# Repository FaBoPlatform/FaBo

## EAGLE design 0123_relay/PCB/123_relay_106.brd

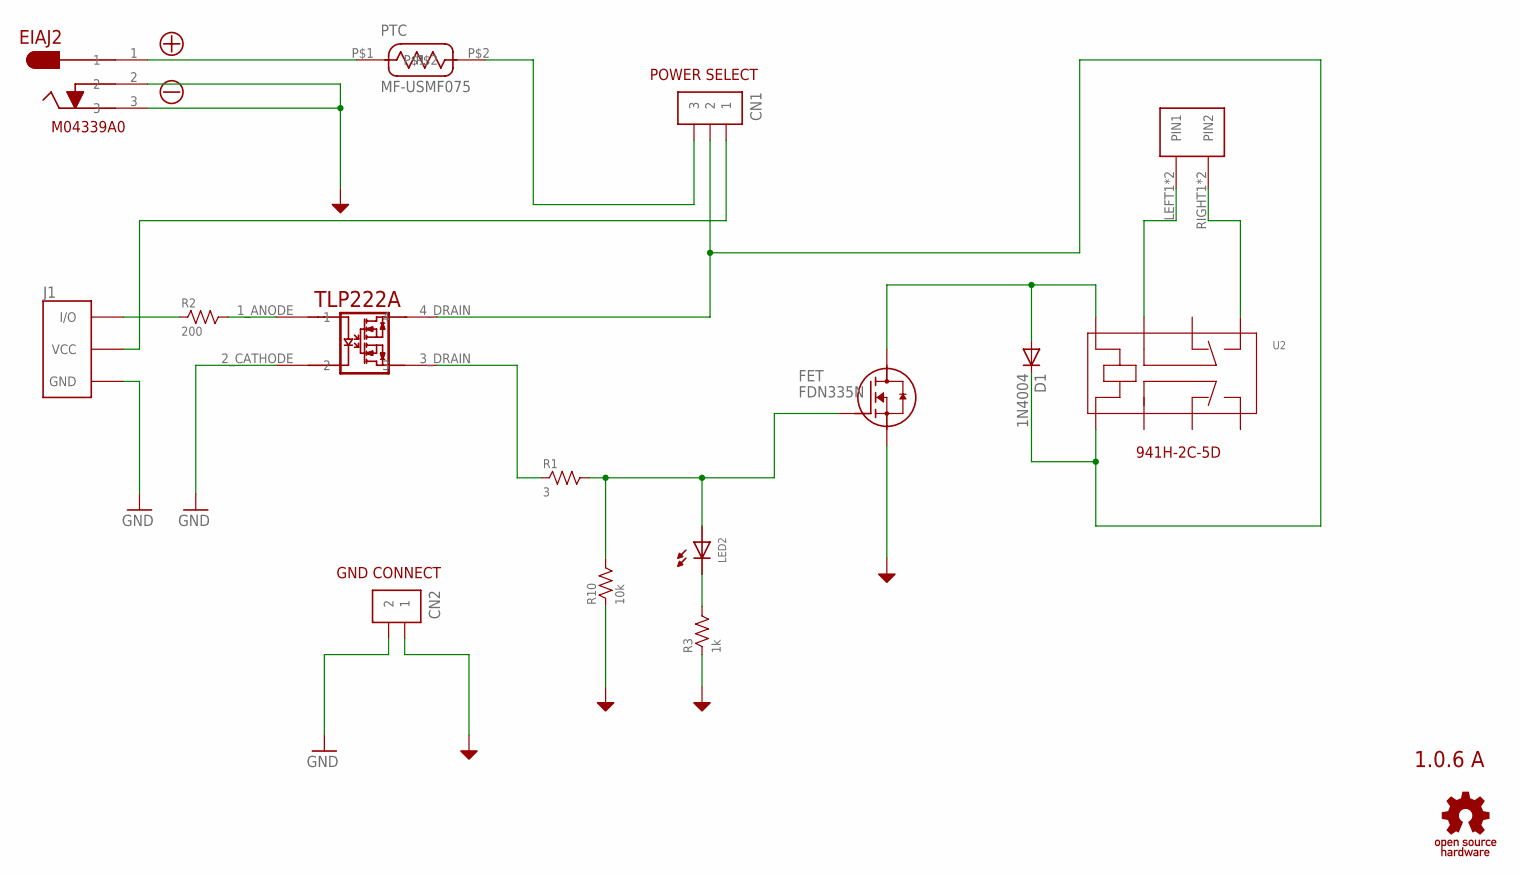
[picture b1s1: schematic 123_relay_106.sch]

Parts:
CN1: PIN_HEADER_1X3; PIN_1X3
CN2: PIN_HEADER_1X2; PIN_1X2
D1: 1N4004; DO41-10
FET: FDN335N; FDN335
J1: FABO_BRICK_3PIN-LONG; FABO_BRICK_3PIN_LONG
LED2: LED-0603; 0603
PTC: MF-USMF075
R1: 3; 0603-NARROW
R2: 200; 0603-NARROW
R3: 1k; 0603-NARROW
R10: 10k; 0603-NARROW
RELAY2: ML-1400-S1
U2: 941-RELAY; 941_RELAY
U$2: LOGO_OSHW-M_BOTTOM; LOGO_OSHW_M_BOTTOM
U$7: M04339A0
U$9: TLP222A

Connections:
GND: CN2.2, J1.GND, U$9.2_CATHODE (2)
GND_SECONDARY: CN2.1, FET.2:S (S), R3.1, R10.1, U$7.2, U$7.3
unnamed: J1.I/O, R2.1
unnamed: RELAY2.LEFT1 (PIN1), RELAY2.LEFT2 (PIN1), U2.13
unnamed: RELAY2.RIGHT1 (PIN2), RELAY2.RIGHT2 (PIN2), U2.9
unnamed: R2.2, U$9.1_ANODE (1)
unnamed: CN1.1, J1.VCC
unnamed: LED2.CATHODE, R3.2
unnamed: CN1.3, PTC.P$2
unnamed: CN1.2, D1.C, U2.1, U$9.4_DRAIN (4)
unnamed: PTC.P$1, U$7.1
unnamed: D1.A, FET.3:D (D), U2.16
unnamed: R1.1, U$9.3_DRAIN (3)
RELAY02: FET.1:G (G), LED2.ANODE, R1.2, R10.2

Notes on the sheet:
1.0.6 A
POWER SELECT
GND CONNECT
941H-2C-5D

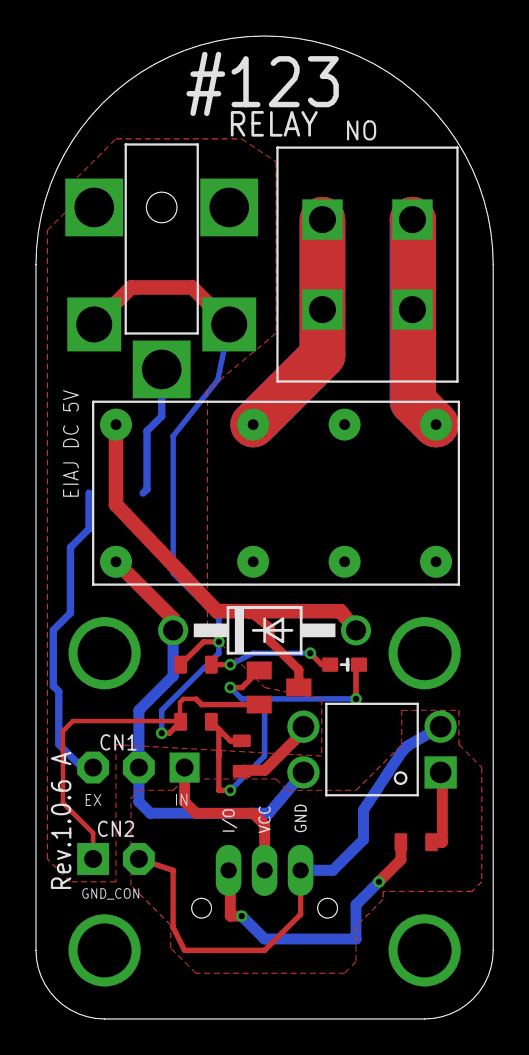
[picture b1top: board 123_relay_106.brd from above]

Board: 2 copper layers, 25.4 x 54.6 mm, 16 parts (1 on the bottom side), 14 nets.

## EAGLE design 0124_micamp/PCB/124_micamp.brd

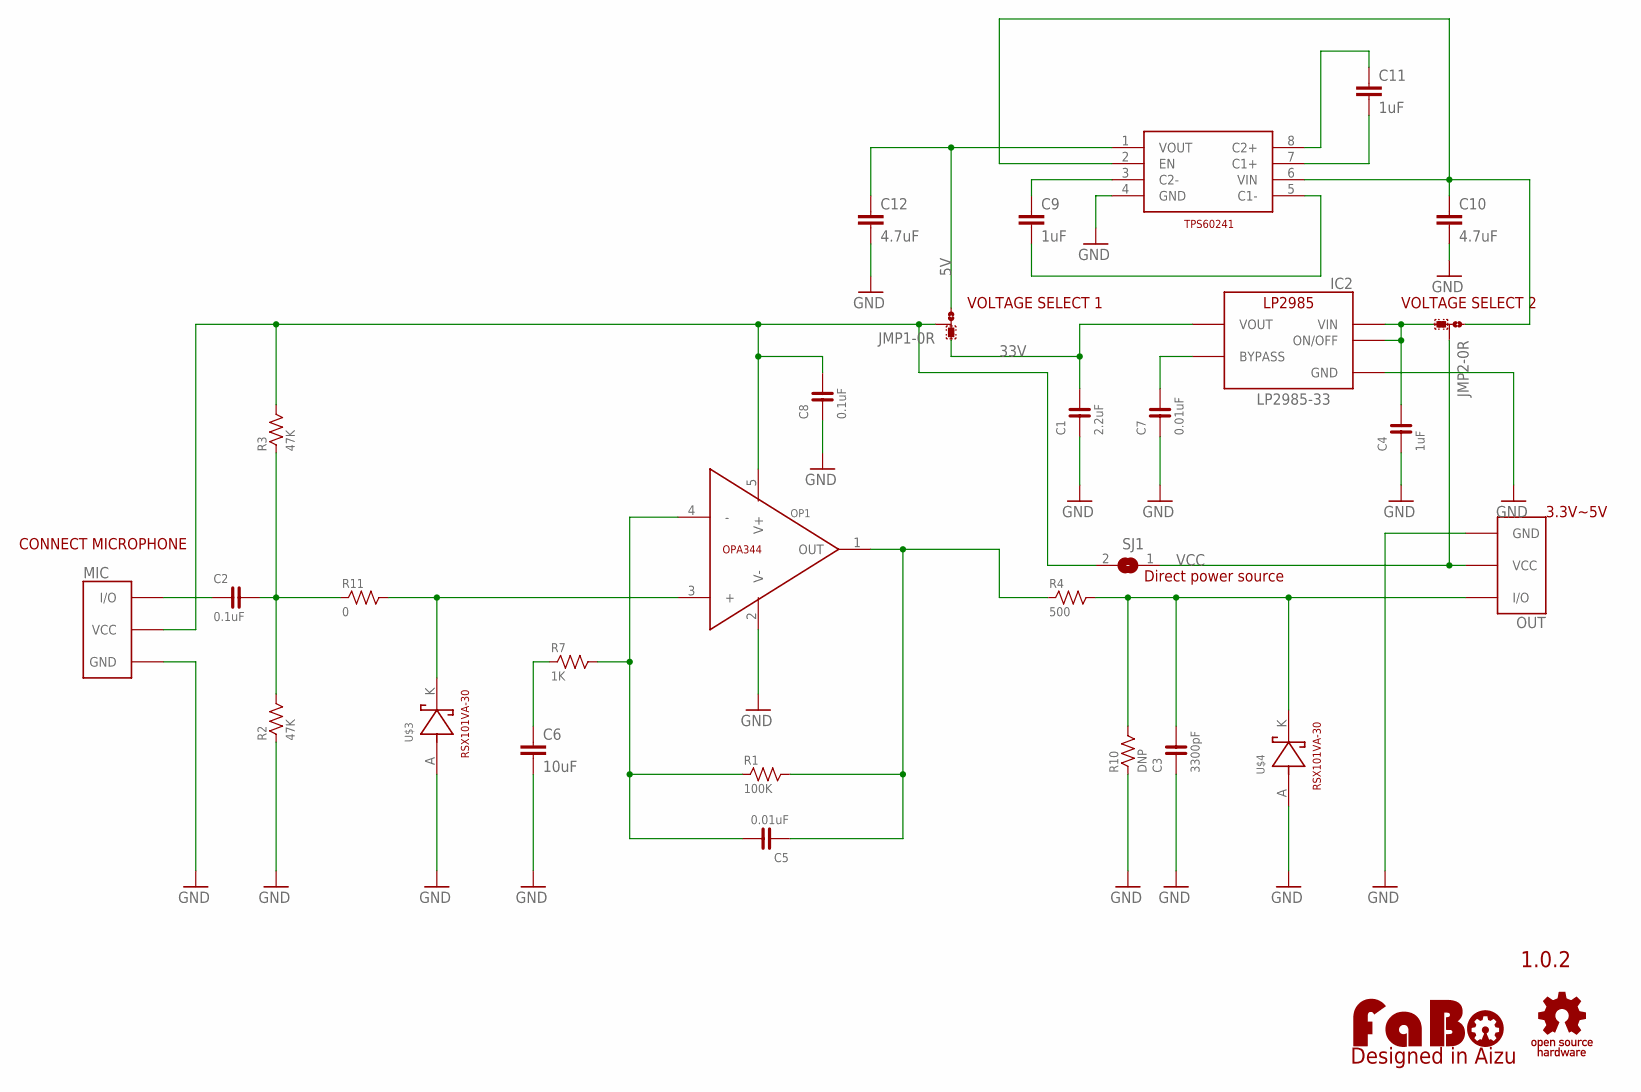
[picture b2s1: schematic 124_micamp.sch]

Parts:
C1: 2.2uF; 0603
C2, C8: 0.1uF; 0603
C3: 3300pF; 0603
C4: 1uF; 0603
C5, C7: 0.01uF; 0603
C6: 10uF; C1206K
C9, C11: 1uF; C2012
C10, C12: 4.7uF; C2012
IC2: LP2985-33; SOT-23-5
JMP1, JMP2: 0R-JUMPA; A0R-JMP
LOGO1: LOGO_FABO-S; LOGO_FABO_S
MIC: FABO_BRICK_3PIN-S03B-PASK-2; FABO_BRICK_3PIN_S03B-PASK-2
OP1: OPA344; SOT23-5
OUT: FABO_BRICK_3PIN-S03B-PASK-2; FABO_BRICK_3PIN_S03B-PASK-2
R1: 100K; 0603
R2, R3: 47K; 0603
R4: 500; 0603
R7: 1K; 0603
R10: DNP; 0603
R11: 0; 0603
SJ1: SJ
U$2: LOGO_OSHW-S_BOTTOM; LOGO_OSHW_S_BOTTOM
U$3, U$4: RSX101VA-30
U$5: TPS60241(VSSOP8); VSSOP8

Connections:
5V: C12.1, JMP1.3, U$5.1 (VOUT)
33V: C1.2, IC2.5 (VOUT), JMP1.1
GND: C1.1, C3.1, C4.1, C6.2, C7.1, C8.1, C10.2, C12.2, IC2.2 (GND), MIC.GND, OP1.2 (V-), OUT.GND, R2.1, R10.1, U$3.A (ANODE), U$4.A (ANODE), U$5.4 (GND)
unnamed: OP1.3 (+), R11.2, U$3.K (CATHODE)
unnamed: C2.1, MIC.I/O
unnamed: C5.2, OP1.4 (-), R1.1, R7.2
unnamed: C6.1, R7.1
unnamed: C5.1, OP1.1 (OUT), R1.2, R4.1
unnamed: C7.2, IC2.4 (BYPASS)
unnamed: C2.2, R2.2, R3.1, R11.1
unnamed: C3.2, OUT.I/O, R4.2, R10.2, U$4.K (CATHODE)
unnamed: C9.1, U$5.3 (C2-)
unnamed: C9.2, U$5.5 (C1-)
unnamed: C11.1, U$5.8 (C2+)
unnamed: C11.2, U$5.7 (C1+)
unnamed: C10.1, JMP2.1, U$5.2 (EN), U$5.6 (VIN)
unnamed: C4.2, IC2.1 (VIN), IC2.3 (ON/OFF), JMP2.3
VCC: JMP2.2, OUT.VCC, SJ1.1
VCC_ON: C8.2, JMP1.2, MIC.VCC, OP1.5 (V+), R3.2, SJ1.2

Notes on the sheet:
LP2985-33
Direct power source
VOLTAGE SELECT 1
VOLTAGE SELECT 2
3.3V~5V
1.0.2
CONNECT MICROPHONE

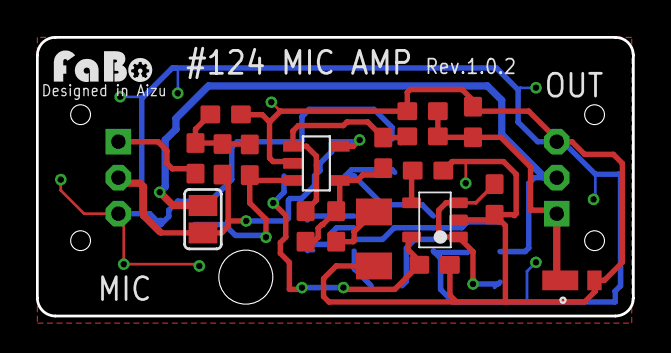
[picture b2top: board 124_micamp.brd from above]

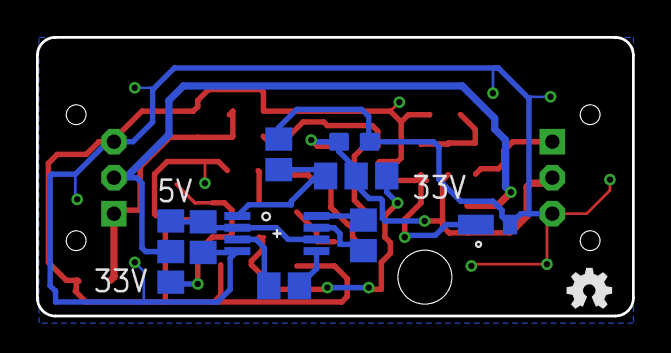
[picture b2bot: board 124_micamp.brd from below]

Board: 2 copper layers, 33.1 x 15.5 mm, 31 parts (9 on the bottom side), 19 nets.

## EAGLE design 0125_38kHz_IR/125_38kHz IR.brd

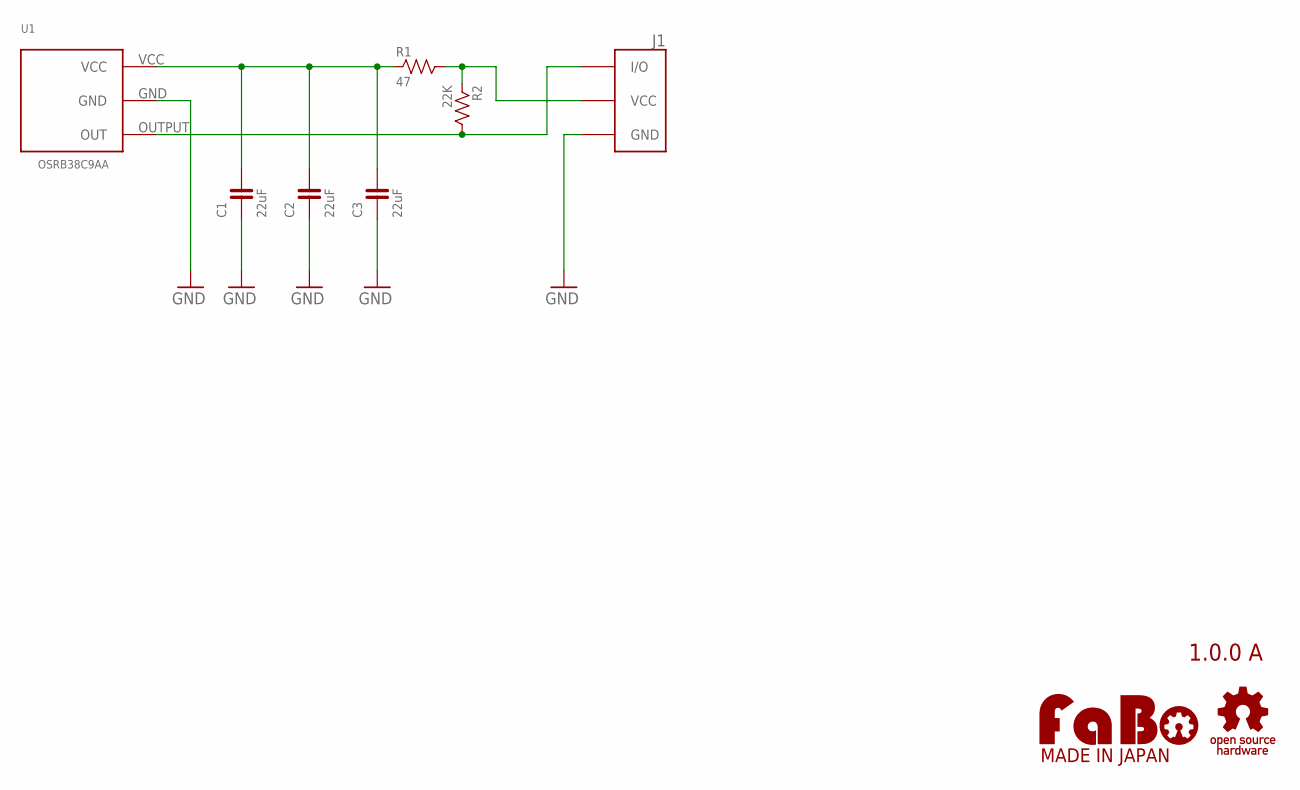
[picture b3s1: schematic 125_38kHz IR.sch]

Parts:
C1, C2, C3: 22uF; 0805
J1: FABO_BRICK_3PIN
R1: 47; 0603
R2: 22K; 0603
U1: OSRB38C9AA
U$2: LOGO_OSHW-M; LOGO_OSHW_M
U$3: LOGO_FABO-M_BOTTOM; LOGO_FABO_MS_BOTTOM

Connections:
GND: C1.1, C2.1, C3.1, J1.GND, U1.GND
unnamed: C1.2, C2.2, C3.2, R1.1, U1.VCC
unnamed: J1.VCC, R1.2, R2.1
unnamed: J1.I/O, R2.2, U1.OUTPUT (OUT)

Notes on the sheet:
1.0.0 A

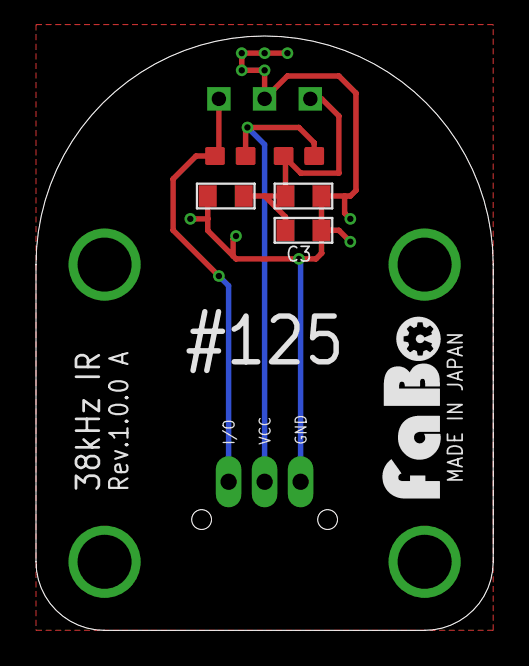
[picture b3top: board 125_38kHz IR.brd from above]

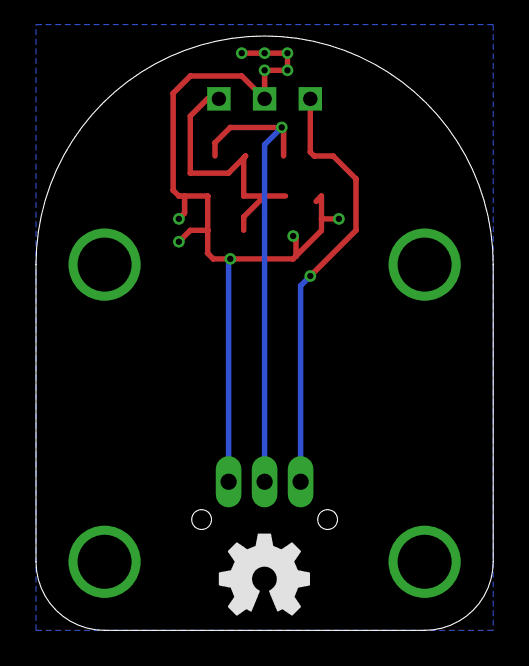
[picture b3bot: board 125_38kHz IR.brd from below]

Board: 2 copper layers, 25.4 x 33.0 mm, 9 parts (2 on the bottom side), 4 nets.

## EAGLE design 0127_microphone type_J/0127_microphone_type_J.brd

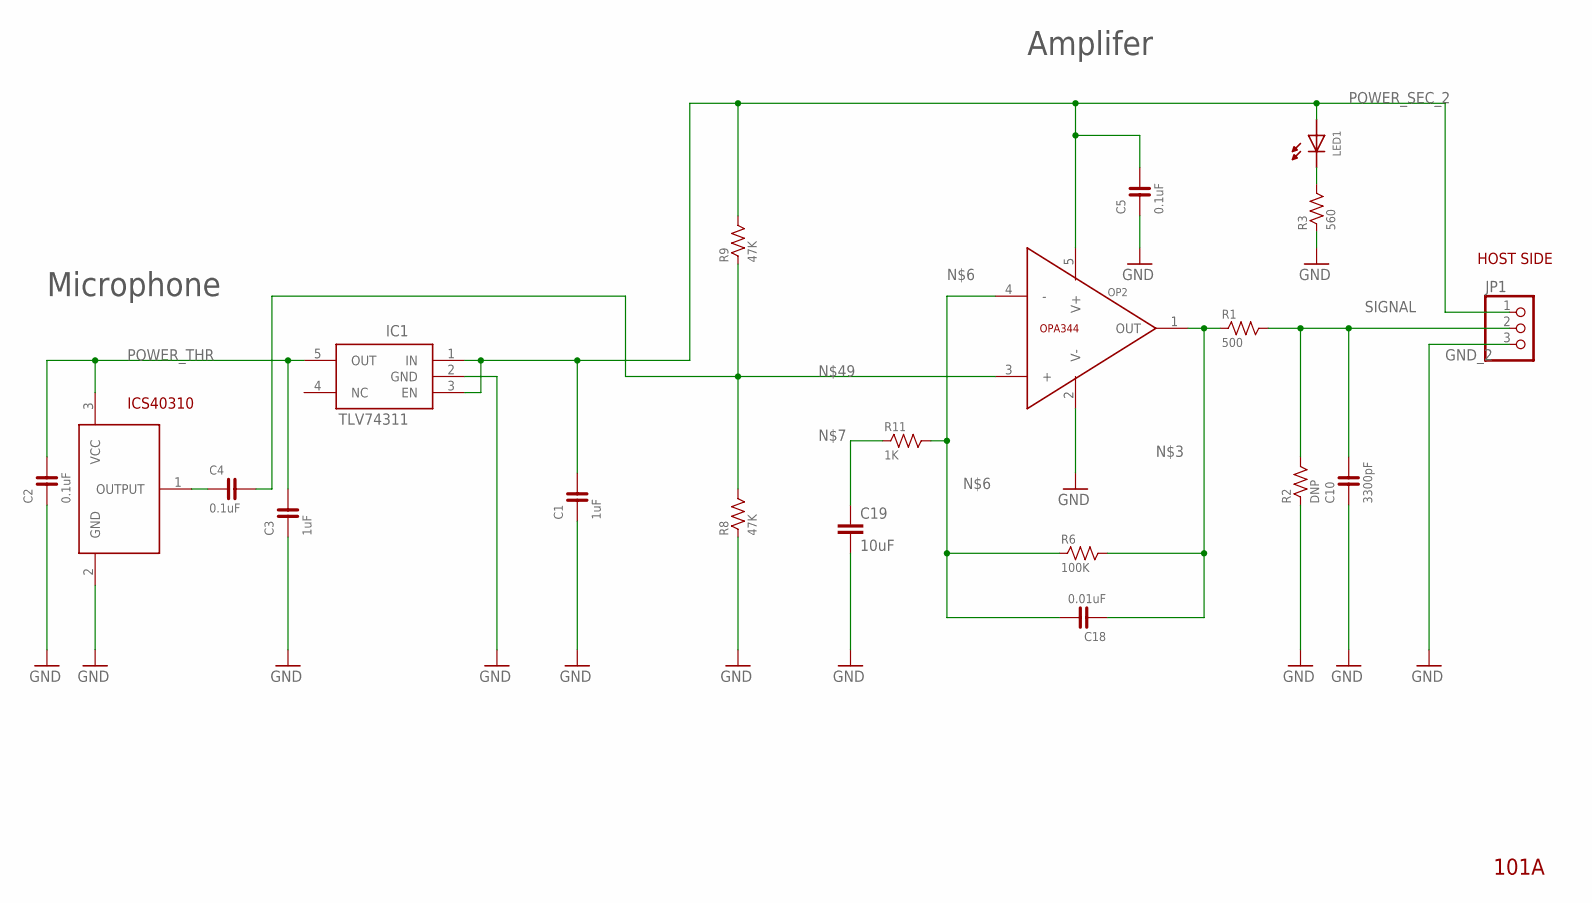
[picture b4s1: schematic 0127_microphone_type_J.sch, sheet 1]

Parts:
C1, C3: 1uF; 0603
C2, C4, C5: 0.1uF; 0603
C10: 3300pF; 0603
C18: 0.01uF; 0603
C19: 10uF; C1206K
IC1: TLV74311; SOT-23-5
ICS40310: ANALOG-MICICS40310; ICS40310
JP1: PINHD-1X3; 1X03
LED1: LED-0603-NARROW; 0603-NARROW
OP2: OPA344; SOT23-5
R1: 500; 0603
R2: DNP; 0603
R3: 560; 0603
R6: 100K; 0603
R8, R9: 47K; 0603
R11: 1K; 0603

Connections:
GND_2: C1.1, C2.1, C3.1, C5.1, C10.1, C19.2, IC1.2 (GND), ICS40310.2 (GND), JP1.3, OP2.2 (V-), R2.1, R3.1, R8.1
unnamed: C18.1, OP2.1 (OUT), R1.1, R6.2
unnamed: C4.1, ICS40310.1 (OUTPUT)
unnamed: LED1.CATHODE, R3.2
unnamed: C18.2, OP2.4 (-), R6.1, R11.2
unnamed: C19.1, R11.1
unnamed: C4.2, OP2.3 (+), R8.2, R9.1
POWER_SEC_2: C1.2, C5.2, IC1.1 (IN), IC1.3 (EN), JP1.1, LED1.ANODE, OP2.5 (V+), R9.2
POWER_THR: C2.2, C3.2, IC1.5 (OUT), ICS40310.3 (VCC)
SIGNAL: C10.2, JP1.2, R1.2, R2.2

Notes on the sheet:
Microphone
ICS40310
101A
Amplifer
HOST SIDE

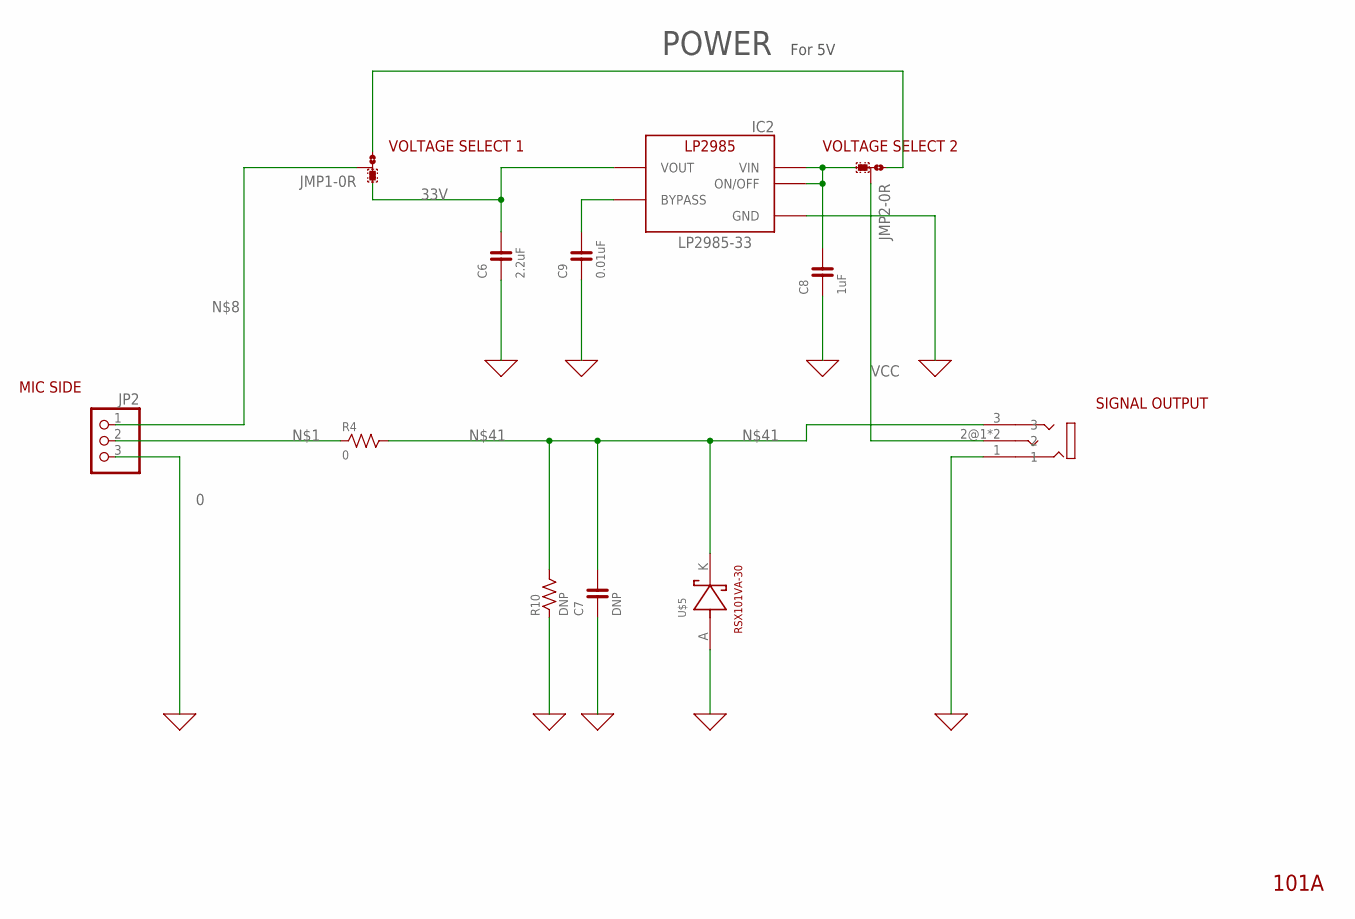
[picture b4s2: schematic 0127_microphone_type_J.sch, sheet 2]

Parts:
C6: 2.2uF; 0603
C7: DNP; 0603
C8: 1uF; 0603
C9: 0.01uF; 0603
IC2: LP2985-33; SOT-23-5
JMP1, JMP2: 0R-JUMPA; A0R-JMP
JP2: PINHD-1X3; 1X03
R4: 0; 0603
R10: DNP; 0603
U$4: MJ8435
U$5: RSX101VA-30

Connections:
0: C6.1, C7.1, C8.1, C9.1, IC2.2 (GND), JP2.3, R10.1, U$4.1, U$5.A (ANODE)
33V: C6.2, IC2.5 (VOUT), JMP1.1
unnamed: JP2.2, R4.1
unnamed: JMP1.3, JMP2.1
unnamed: JMP1.2, JP2.1
unnamed: C7.2, R4.2, R10.2, U$4.3, U$5.K (CATHODE)
unnamed: C9.2, IC2.4 (BYPASS)
unnamed: C8.2, IC2.1 (VIN), IC2.3 (ON/OFF), JMP2.3
VCC: JMP2.2, U$4.2@1 (2), U$4.2@2 (2)

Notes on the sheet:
LP2985-33
VOLTAGE SELECT 1
VOLTAGE SELECT 2
101A
SIGNAL OUTPUT
MIC SIDE
POWER
For 5V

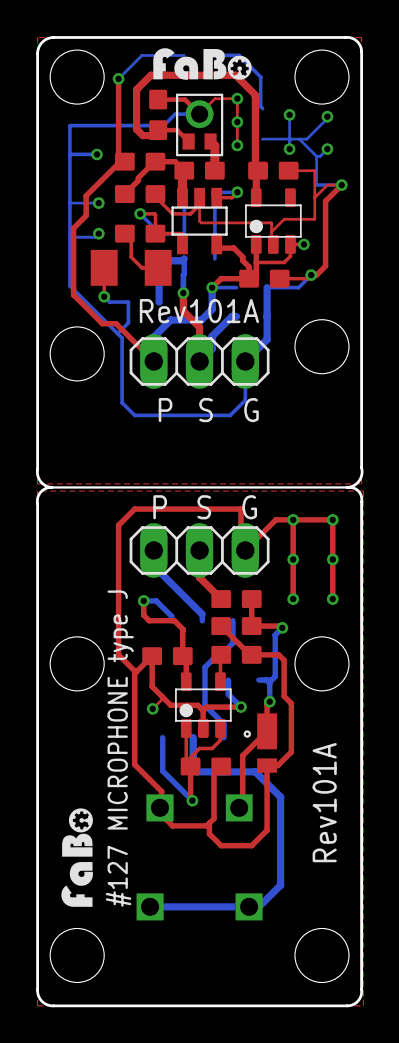
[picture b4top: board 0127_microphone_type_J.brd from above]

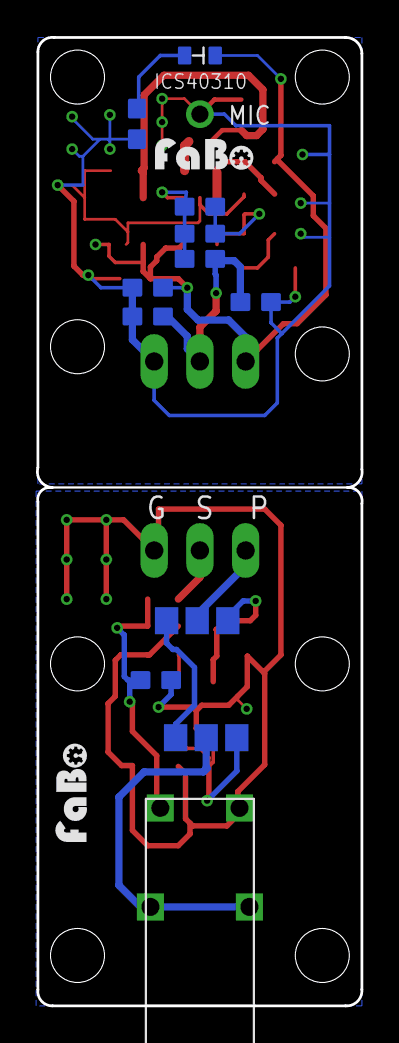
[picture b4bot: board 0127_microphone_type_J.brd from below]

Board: 2 copper layers, 18.0 x 53.8 mm, 36 parts (14 on the bottom side), 19 nets.

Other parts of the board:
U$2, U$6, U$7, U$8: LOGO_FABO_S

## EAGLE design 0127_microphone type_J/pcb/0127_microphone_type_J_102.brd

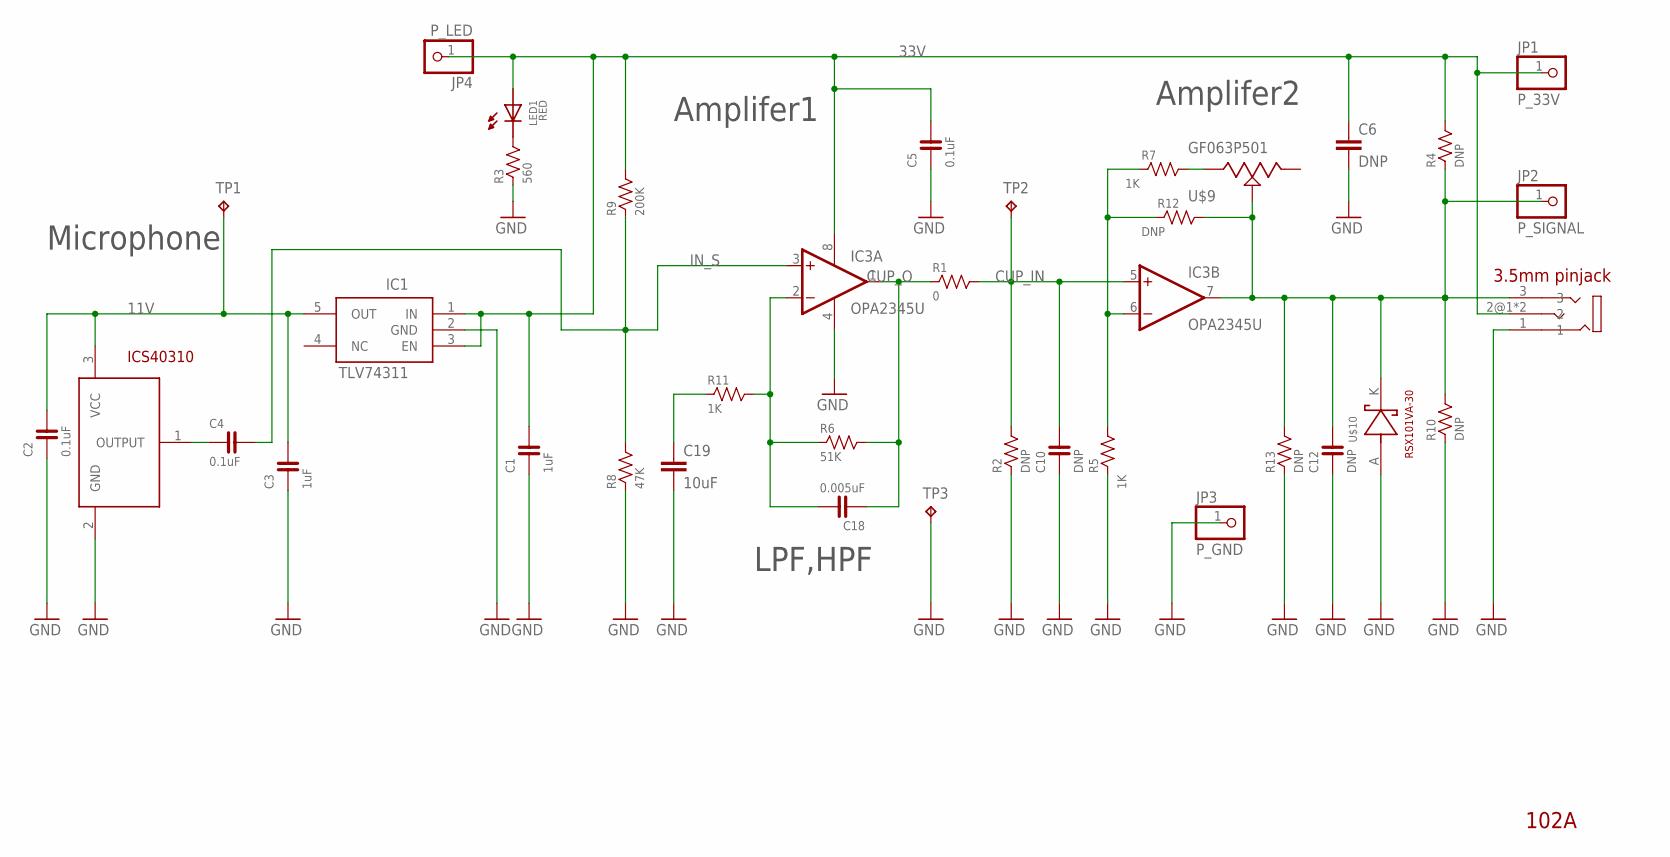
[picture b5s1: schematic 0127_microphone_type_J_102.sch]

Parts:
C1, C3: 1uF; 0603
C2, C4, C5: 0.1uF; 0603
C6: DNP; C1206K
C10, C12: DNP; 0603
C18: 0.005uF; 0603
C19: 10uF; C1206K
IC1: TLV74311; SOT-23-5
IC3: OPA2345U; SO08
ICS40310: ANALOG-MICICS40310; ICS40310
JP1: P_33V; 1X01
JP2: P_SIGNAL; 1X01
JP3: P_GND; 1X01
JP4: P_LED; 1X01
LED1: RED; 0603-NARROW
R1: 0; 0603
R2, R4, R10, R12, R13: DNP; 0603
R3: 560; 0603
R5, R7, R11: 1K; 0603
R6: 51K; 0603
R8: 47K; 0603
R9: 200K; 0603
TP1, TP2, TP3: TPB1,27; B1,27
U$9: GF063P501; GF063P103
U$10: RSX101VA-30
U$11: MJ8435

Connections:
11V: C2.2, C3.2, IC1.5 (OUT), ICS40310.3 (VCC), TP1.TP
33V: C1.2, C5.2, C6.1, IC1.1 (IN), IC1.3 (EN), IC3.8 (V+), JP1.1, JP4.1, LED1.ANODE, R4.2, R9.2, U$11.2@1 (2), U$11.2@2 (2)
CUP_IN: C10.2, IC3.5 (+IN), R1.2, R2.2, TP2.TP
CUP_O: C18.1, IC3.1 (OUT), R1.1, R6.2
FB1: C18.2, IC3.2 (-IN), R6.1, R11.2
FB2: IC3.6 (-IN), R5.2, R7.1, R12.1
GND: C1.1, C2.1, C3.1, C5.1, C6.2, C10.1, C12.1, C19.2, IC1.2 (GND), IC3.4 (V-), ICS40310.2 (GND), JP3.1, R2.1, R3.1, R5.1, R8.1, R10.1, R13.1, TP3.TP, U$10.A (ANODE), U$11.1
IN_S: C4.2, IC3.3 (+IN), R8.2, R9.1
MIC_O: C4.1, ICS40310.1 (OUTPUT)
unnamed: LED1.CATHODE, R3.2
unnamed: C19.1, R11.1
unnamed: R7.2, U$9.3
OUT_S: C12.2, IC3.7 (OUT), JP2.1, R4.1, R10.2, R12.2, R13.2, U$9.2, U$10.K (CATHODE), U$11.3

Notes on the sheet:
Microphone
ICS40310
102A
Amplifer1
LPF,HPF
Amplifer2
3.5mm pinjack

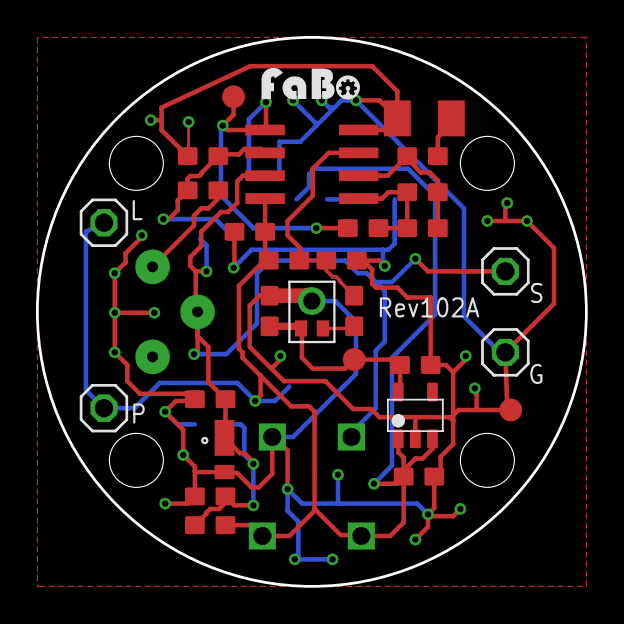
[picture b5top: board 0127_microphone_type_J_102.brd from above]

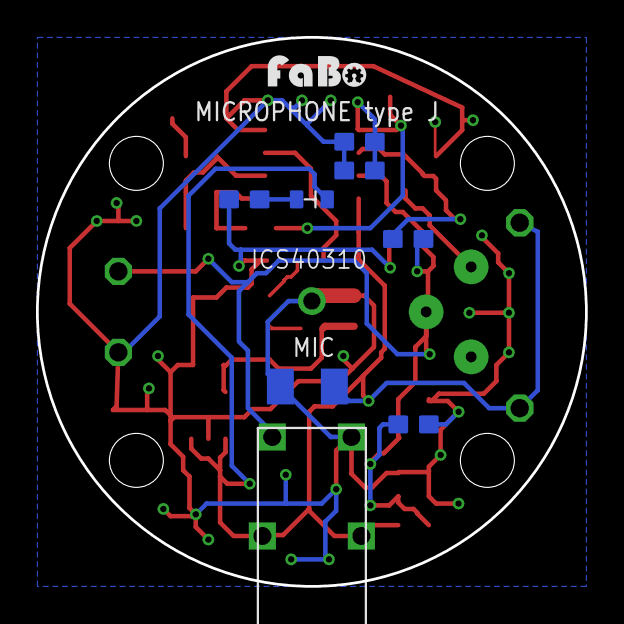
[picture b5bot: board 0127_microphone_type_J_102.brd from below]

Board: 2 copper layers, 30.5 x 30.5 mm, 39 parts (9 on the bottom side), 13 nets.

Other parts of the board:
U$2, U$8: LOGO_FABO_S

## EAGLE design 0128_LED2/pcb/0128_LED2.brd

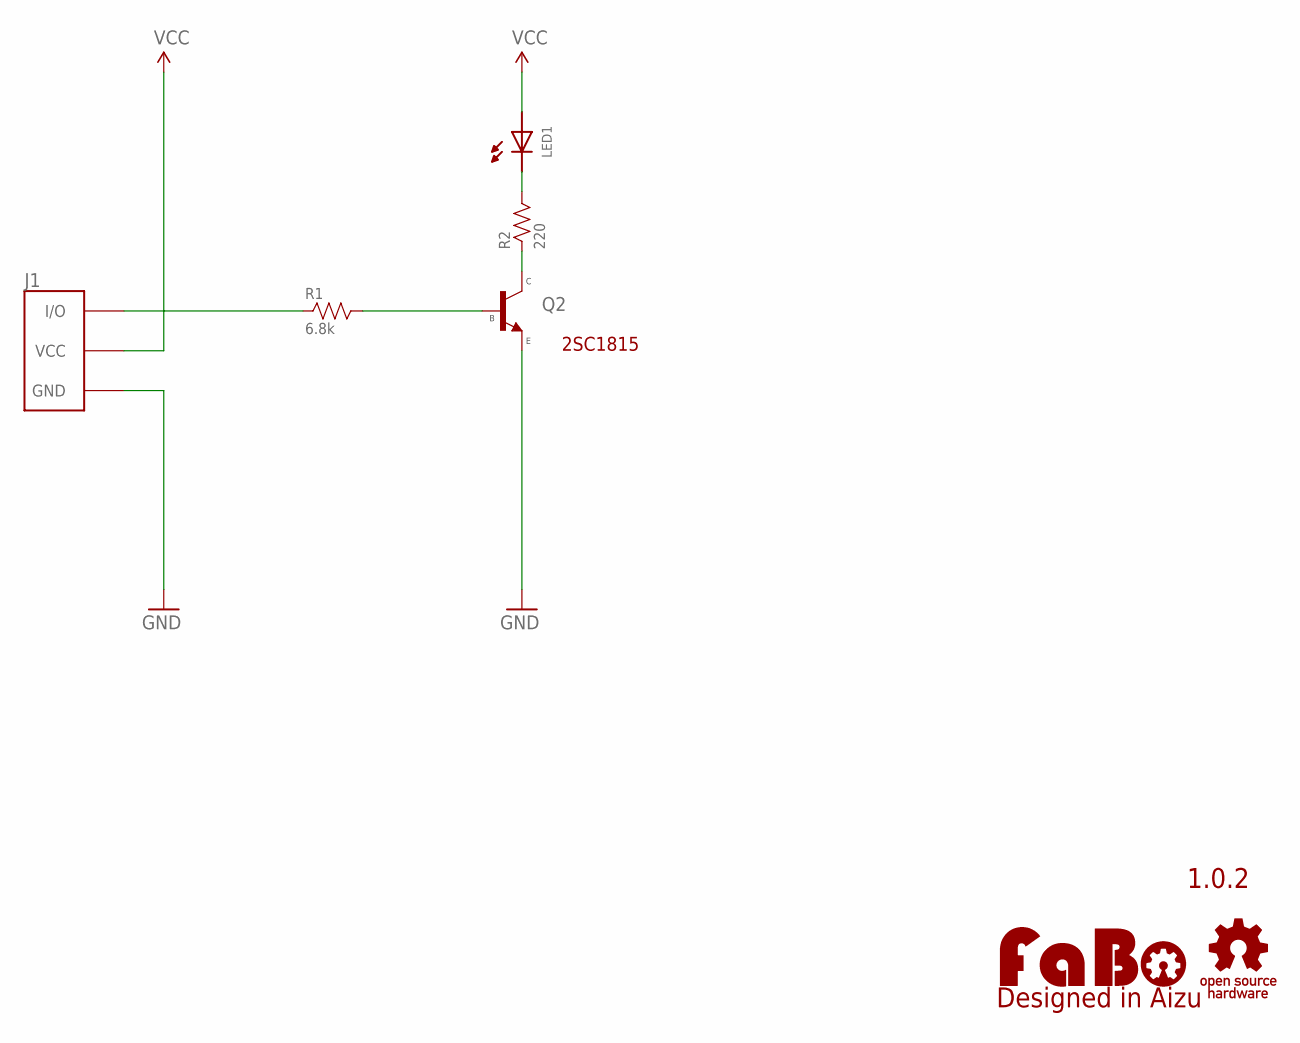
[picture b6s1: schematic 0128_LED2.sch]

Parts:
J1: FABO_BRICK_3PIN
LED1: LED-5MM; LED_5MM
LOGO1: LOGO_FABO-M; LOGO_FABO_M
Q2: NPN-2SC1815; TO-92
R1: 6.8k; AXL-REGULAR
R2: 220; AXL-REGULAR
U$6: LOGO_OSHW-M_BOTTOM; LOGO_OSHW_M_BOTTOM

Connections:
GND: J1.GND, Q2.1 (E)
unnamed: J1.I/O, R1.1
unnamed: Q2.2 (C), R2.1
unnamed: LED1.K (CATHODE), R2.2
unnamed: Q2.3 (B), R1.2
VCC: J1.VCC, LED1.A (ANODE)

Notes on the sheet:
1.0.2
2SC1815

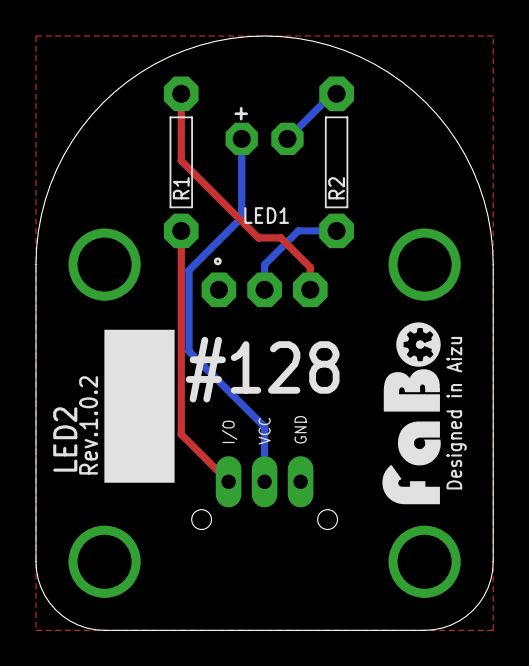
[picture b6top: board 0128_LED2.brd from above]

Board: 2 copper layers, 25.4 x 33.0 mm, 7 parts (0 on the bottom side), 6 nets.

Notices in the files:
parts and their libraries:
FaBo-etc: Released under the Creative Commons Attribution-ShareAlike 4.0 License
https://creativecommons.org/licenses/by-sa/4.0
FaBo-etc: Released under the Creative Commons
